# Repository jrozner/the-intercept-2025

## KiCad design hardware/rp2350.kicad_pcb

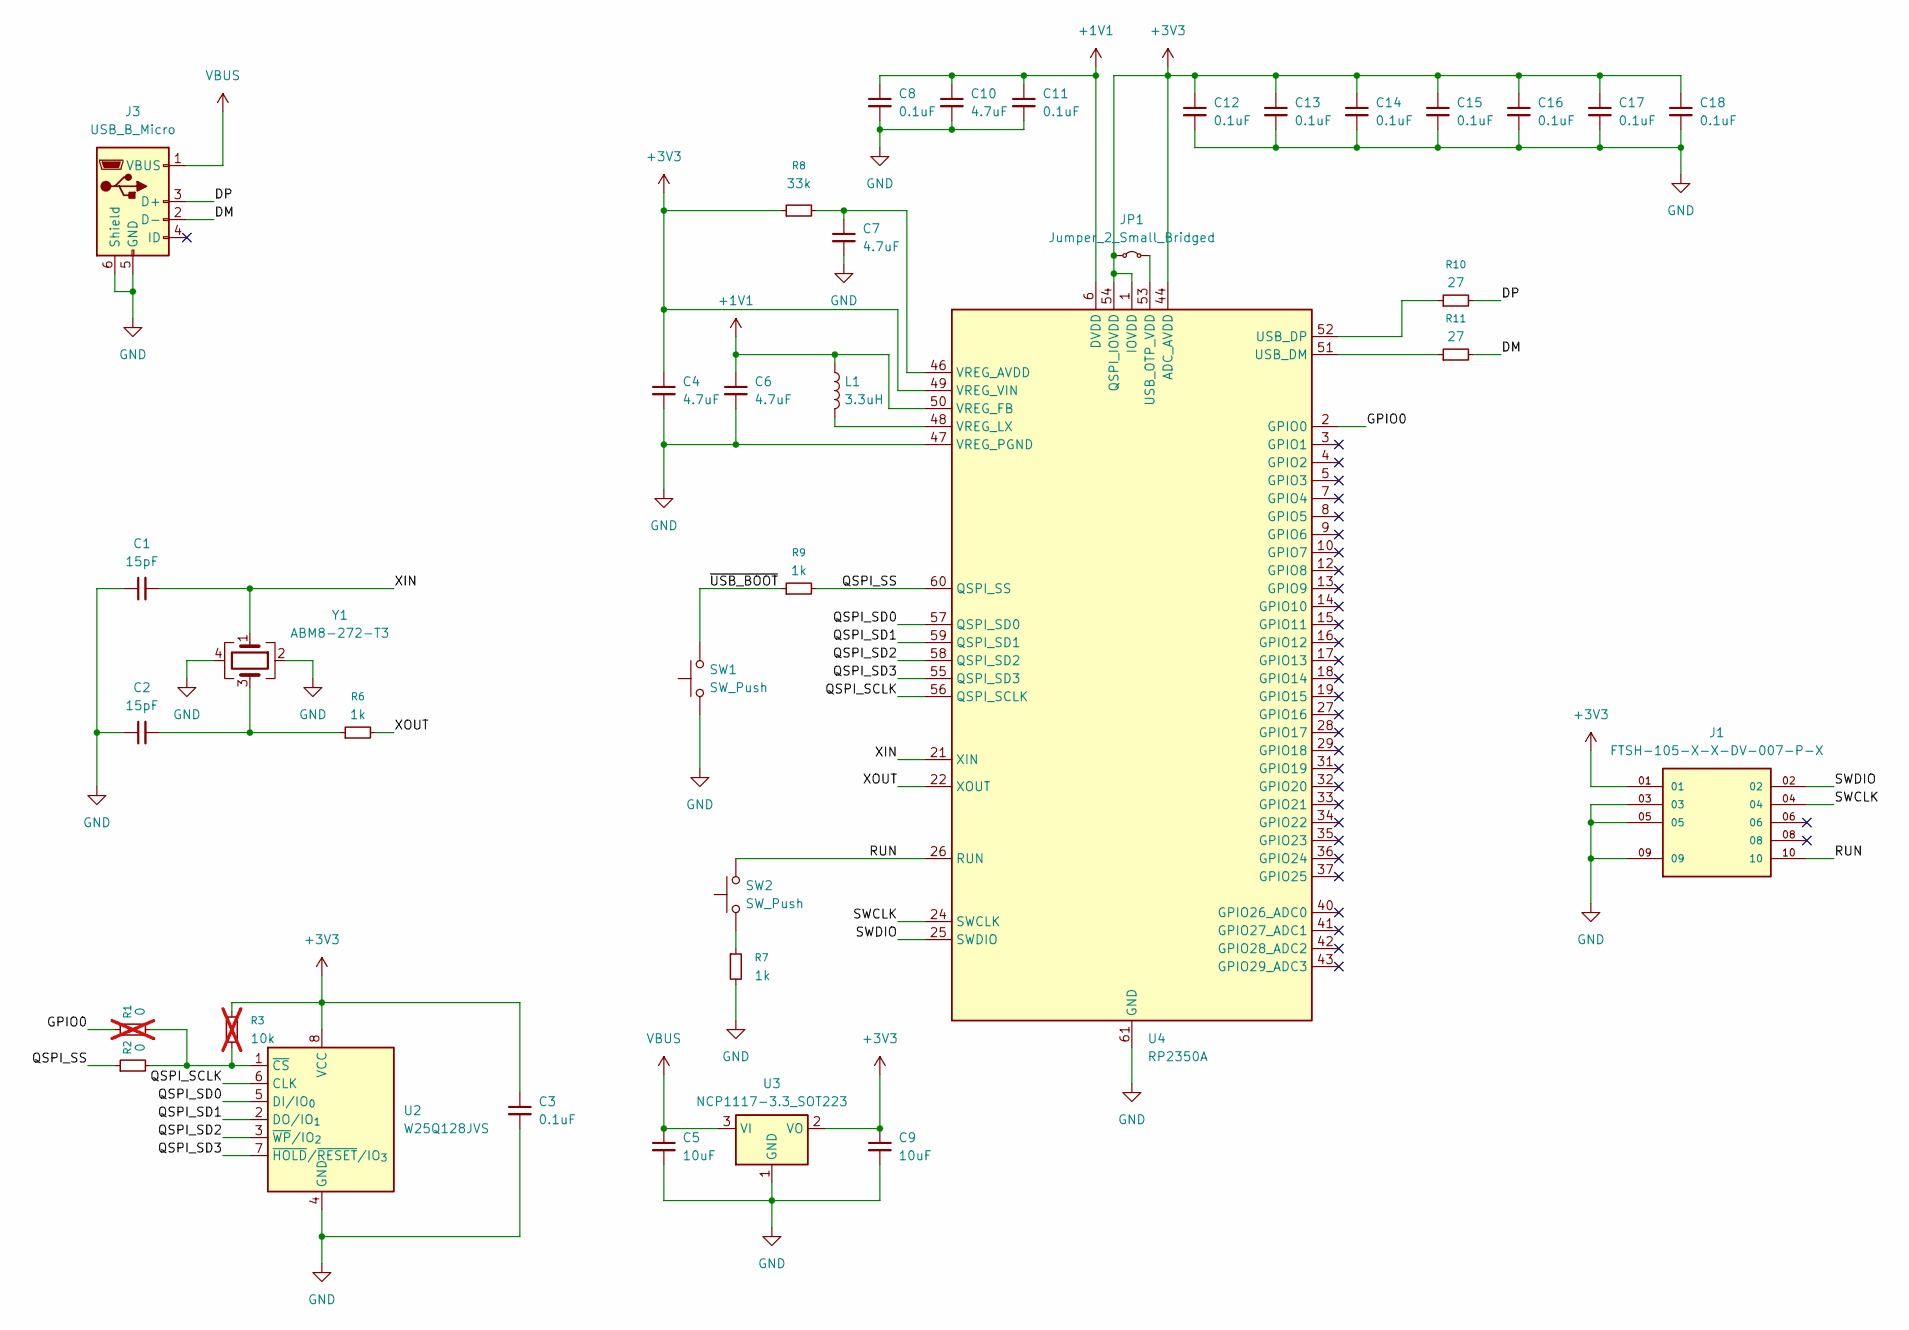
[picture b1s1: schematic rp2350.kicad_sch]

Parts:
C1, C2: 15pF; C_0603_1608Metric
C3, C8, C11, C12, C13, C14, C15, C16, C17, C18: 0.1uF; C_0603_1608Metric
C4, C6, C7, C10: 4.7uF; C_0603_1608Metric
C5, C9: 10uF; C_0603_1608Metric
J1: FTSH-105-X-X-DV-007-P-X; SAMTEC_FTSH-105-X-X-DV-007-P-X; PARTREV H
J3: USB_B_Micro; USB_Micro-B_Amphenol_10103594-0001LF_Horizontal
JP1: Jumper_2_Small_Bridged; SolderJumper-2_P1.3mm_Bridged_Pad1.0x1.5mm
L1: 3.3uH; AOTA-B201610S3R3-101-T
R1: 0; R_0603_1608Metric; not fitted
R2: 0; R_0603_1608Metric
R3: 10k; R_0603_1608Metric; not fitted
R6, R7, R9: 1k; R_0603_1608Metric
R8: 33k; R_0603_1608Metric
R10, R11: 27; R_0603_1608Metric
SW1, SW2: SW_Push; SW_SPST_TL3305A
U2: W25Q128JVS; SOIC-8_5.3x5.3mm_P1.27mm
U3: NCP1117-3.3_SOT223; SOT-223-3_TabPin2
U4: RP2350A; QFN-60-1EP_7x7mm_P0.4mm_EP3.4x3.4mm_ThermalVias
Y1: ABM8-272-T3; Crystal_SMD_3225-4Pin_3.2x2.5mm

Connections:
+1V1: C6.1, C8.1, C10.1, C11.1, L1.1, U4.6 (DVDD), U4.23 (DVDD), U4.39 (DVDD), U4.50 (VREG_FB)
+3V3: C3.1, C4.1, C9.1, C12.1, C13.1, C14.1, C15.1, C16.1, C17.1, C18.1, J1.01, JP1.1 (A), R3.1, R8.1, U2.8 (VCC), U3.2 (VO), U4.1 (IOVDD), U4.11 (IOVDD), U4.20 (IOVDD), U4.30 (IOVDD), U4.38 (IOVDD), U4.44 (ADC_AVDD), U4.45 (IOVDD), U4.49 (VREG_VIN), U4.54 (QSPI_IOVDD)
/DM: J3.2 (D-), R11.2
/DP: J3.3 (D+), R10.2
/GPIO0: R1.1, U4.2 (GPIO0)
/QSPI_SCLK: U2.6 (CLK), U4.56 (QSPI_SCLK)
/QSPI_SD0: U2.5 (DI/IO_{0}), U4.57 (QSPI_SD0)
/QSPI_SD1: U2.2 (DO/IO_{1}), U4.59 (QSPI_SD1)
/QSPI_SD2: U2.3 (~WP/IO_{2}), U4.58 (QSPI_SD2)
/QSPI_SD3: U2.7 (~HOLD/~RESET/IO_{3}), U4.55 (QSPI_SD3)
/QSPI_SS: R2.1, R9.2, U4.60 (QSPI_SS)
/RUN: J1.10, SW2.2, U4.26 (RUN)
/SWCLK: J1.04, U4.24 (SWCLK)
/SWDIO: J1.02, U4.25 (SWDIO)
/XIN: C1.2, U4.21 (XIN), Y1.1
/XOUT: R6.2, U4.22 (XOUT)
/~USB_BOOT: R9.1, SW1.2
GND: C1.1, C2.1, C3.2, C4.2, C5.2, C6.2, C7.2, C8.2, C9.2, C10.2, C11.2, C12.2, C13.2, C14.2, C15.2, C16.2, C17.2, C18.2, J1.03, J1.05, J1.09, J3.5 (GND), J3.6 (Shield), R7.2, SW1.1, U2.4 (GND), U3.1 (GND), U4.47 (VREG_PGND), U4.61 (GND), Y1.2, Y1.4
unnamed: C2.2, R6.1, Y1.3
unnamed: JP1.2 (B), U4.53 (USB_OTP_VDD)
unnamed: R7.1, SW2.1
unnamed: R1.2, R2.2, R3.2, U2.1 (~CS)
unnamed: R11.1, U4.51 (USB_DM)
unnamed: R10.1, U4.52 (USB_DP)
unnamed: C7.1, R8.2, U4.46 (VREG_AVDD)
unnamed: L1.2, U4.48 (VREG_LX)
VBUS: C5.1, J3.1 (VBUS), U3.3 (VI)

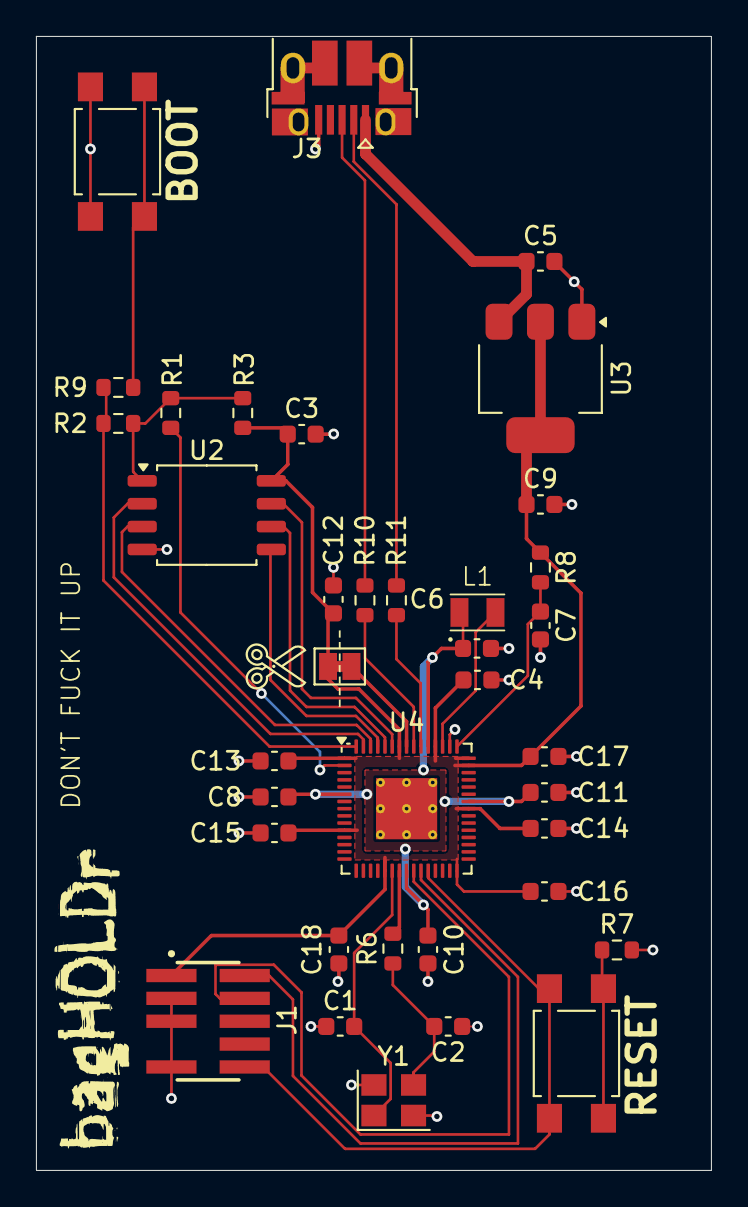
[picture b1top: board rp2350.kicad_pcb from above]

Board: 2 copper layers, 37.5 x 63.0 mm, 37 parts (0 on the bottom side), 27 nets.

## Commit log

2025-03-17 Add gitignore
2025-03-17 Add scripts to generate keys
2025-04-05 Add hello world code
2025-04-17 Working firmware
2025-04-18 a build script for those who hate cding away their precious time
2025-04-24 Add first revision of hardware
2025-04-26 basic USB IO
2025-04-27 basic menuing
2025-04-27 added admin challenge / mode
2025-04-27 added -f reboot to picotool command
2025-04-27 fixed build system
2025-04-27 added RugCoin challenge and solution
2025-04-27 god damnit jk
2025-04-27 added stdlib.h
2025-04-27 added md5
2025-04-27 menu stuff messy but getting there
2025-04-27 added inflatocash menu option
2025-04-27 moar menu
2025-05-05 added inflatocash challenge
2025-05-05 whatever
2025-05-05 added chain
2025-05-05 full menu stuff working
2025-05-05 updated warning string to hex
2025-05-05 fixed mining includes
2025-05-06 added pico-sdk-patch folder
2025-05-14 hid answer in rugcoin
2025-05-19 Secure boot and OTP
2025-05-19 More updates
2025-05-19 More fixes
2025-05-22 Final fixes
2025-05-25 Fix patch
